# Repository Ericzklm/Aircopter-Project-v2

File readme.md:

# Aircopter Project

This project was done in association with the IEEE Student Branch on the UCLA campus.
This is the second iteration of the project. Due to the 2020 global pandemic, this
project was cut short for the 2019-2020 academic year and will resume in the 2020-
2021 academic year.

The goal of the project was to: 1. Design and assemble a custom PCB for a drone,
2. Write a program to hover the drone, then fly the drone. Because of the nature
of the project, the PCB was required to be small and compact (meaning SMD soldering
was needed) and the program needed to be quick and responsive.

#### Note: 

This version of the project was cut short due to the 2020 pandemic. The code was still
written and the board was still designed and printed but we were not able to assemble
and solder the final product because we were then living off-campus and all campus
activities we're mandated to be put on hold.

### Hardware Selection Choices:

**MCU**: The main chip is the model STM32F405. This was chosen for its ideal balance
between size and functionality. It is able to support all the needed sensors and
motor drivers for our drone and can be powered by a 3.3v supply which closely
matches the 3.7v of standard drone batteries (3.7v is stepped down to 3.3 using
a voltage regulator). Additionally, this chip was more ideal than other chips of
similar style because it handles floating point calculations better which allows
for simplicity and efficiency when writing the program.

**Voltage Regulator**: The voltage regulator used is the LTC3246MPMSE from Linear 
Technology. This component was chosen since it is a buck boost regulator with
the ability to step down or step up voltage as we need in this application. This
component is larger, more expensive, and more complex than the regulator used in
the first iteration but it accomplishes the same purpose while being much easier
to solder onto the board (no heat guns required).

**Wireless Module**: The wireless module used is the nrf24l01 which is standard, easy
to use, and familiar so we used it in this application since it fits well with the
acclerometer module.

**Accelerometer/Gyroscope**: The module used is the mpu6050 which is standard, easy to
use, and familiar so we used it in this application since it fits well with the
wireless module.

**Oscillator**: We opted for an abracon 25mhz crystal oscillator. The frequency fits 
the range of our operation and takes up a relatively small amount of space on
the PCB. In this iteration, a through-hole component was chosen because it could
be added more compactly without needing large pads on the PCB outside the area of
the oscillator.

**Passive Components**: For the resistors, capacitors, and inductors, we primarily
used parts with the package size 0603 which would fit the board without being
overly difficult to solder. Each piece was checked for its operating voltages as 
well as the operating temperatures to make sure no issues would arise. Additonally,
we tried to get components that were less dependent on external passive components
so we could make the PCB more compact/efficient.

### Hardware Design Choices:

**Motors**: In this design, we opted to place the 4 motor JST connectors along the left
side of the board because this would reduce the amount of "prime-real-estate" occupied
by the motor drivers. Also, we saved a significant amount of space on the PCB by
moving the motor drivers to the backside, under the JST rather than having the drivers
being on the same side (which means we cannot overlap the area occupied by the JSTs).

**Battery**: The JST of the battery is placed directly right of the motors. This is
important since its a central component and that position allows it easy access to
the motors and the rest of the PCB.

**Voltage Regulator**: The voltage regulator is placed below the battery JST, also in a
central position. This is key because we are able to define the 3.7V and 3.3V polygons
without complexity, and therefore reduing bottlenecks. Because the voltage regulator
is dependent on several passive components, it is placed in an open space with the
passive components compactly fit around it, without creating any major bottlenecks.

**Polygons**: Because of the location of the voltage divider, we are able to make an easy
distinction between the 3.3v, 3.7v, motor ground, and general ground planes. Everything
left of the voltage regulator is either the 3.7v or motor ground planes while everything
right is either 3.3v or general ground.

**MCU**: We chose to turn the MCU 45 degrees for a few reasons:
  1. Having the MCU turned actually signficantly reduced the bottlenecks as key 
  components had more direct access to the 3.3v plane and we had less "dead-ends" in 
  the plane. This gave extra space to work in that would not present a threat of 
  bottlenecking.
  2. The traces coming out of the MCU can be shorter and more optimized for the key
  components.
  3. We thought it looked neat!

**Oscillator**: The oscillator is placed as physically close to the MCU as possible with
relatively thick traces in order to prevent that signal from being overly distorted.

**Wireless Module/Accelerometer**: Because these two modules are not raised to the same
level, they can be overlapping on the PCB and not cause any issues. The wireless
module is placed along the right side while the accelerometer is placed along the
bottom because this allows for easy access to the respective connections on the MCU.

**Other items**: This includes the programmer and the reset switch. Since neither of them
are crucial in the operation of the drone, they are place along the top with less
direct connections (meaning the traces and planes for key components are better
optimized). Additionally, this iteration includes a tx and rx connection which will
be useful for debugging.

**Bottlenecks**: For this version, we were able to get away with no major bottlenecks
in the planes thanks to the reduction of passive components, better placements,
and the 45 degree MCU.

**Decoupling Capacitors**: The decoupling capacitors are placed in such a way that they
are close to the components they stabalize. This also helped in reducing bottlenecks
as passive components were not cutting up the planes

### Possible Improvements:

Some components are not optimally placed meaning the traces are not direct. This can
be solved by either tweaking the placement or choosing different compatible pins on
the MCU. Also the placement of the motors and battery mean that the lower motors are
further away from the power source, meaning potentially higher noise. Furthermore,
adding some LEDs would be useful for debugging (we have the room to do so).

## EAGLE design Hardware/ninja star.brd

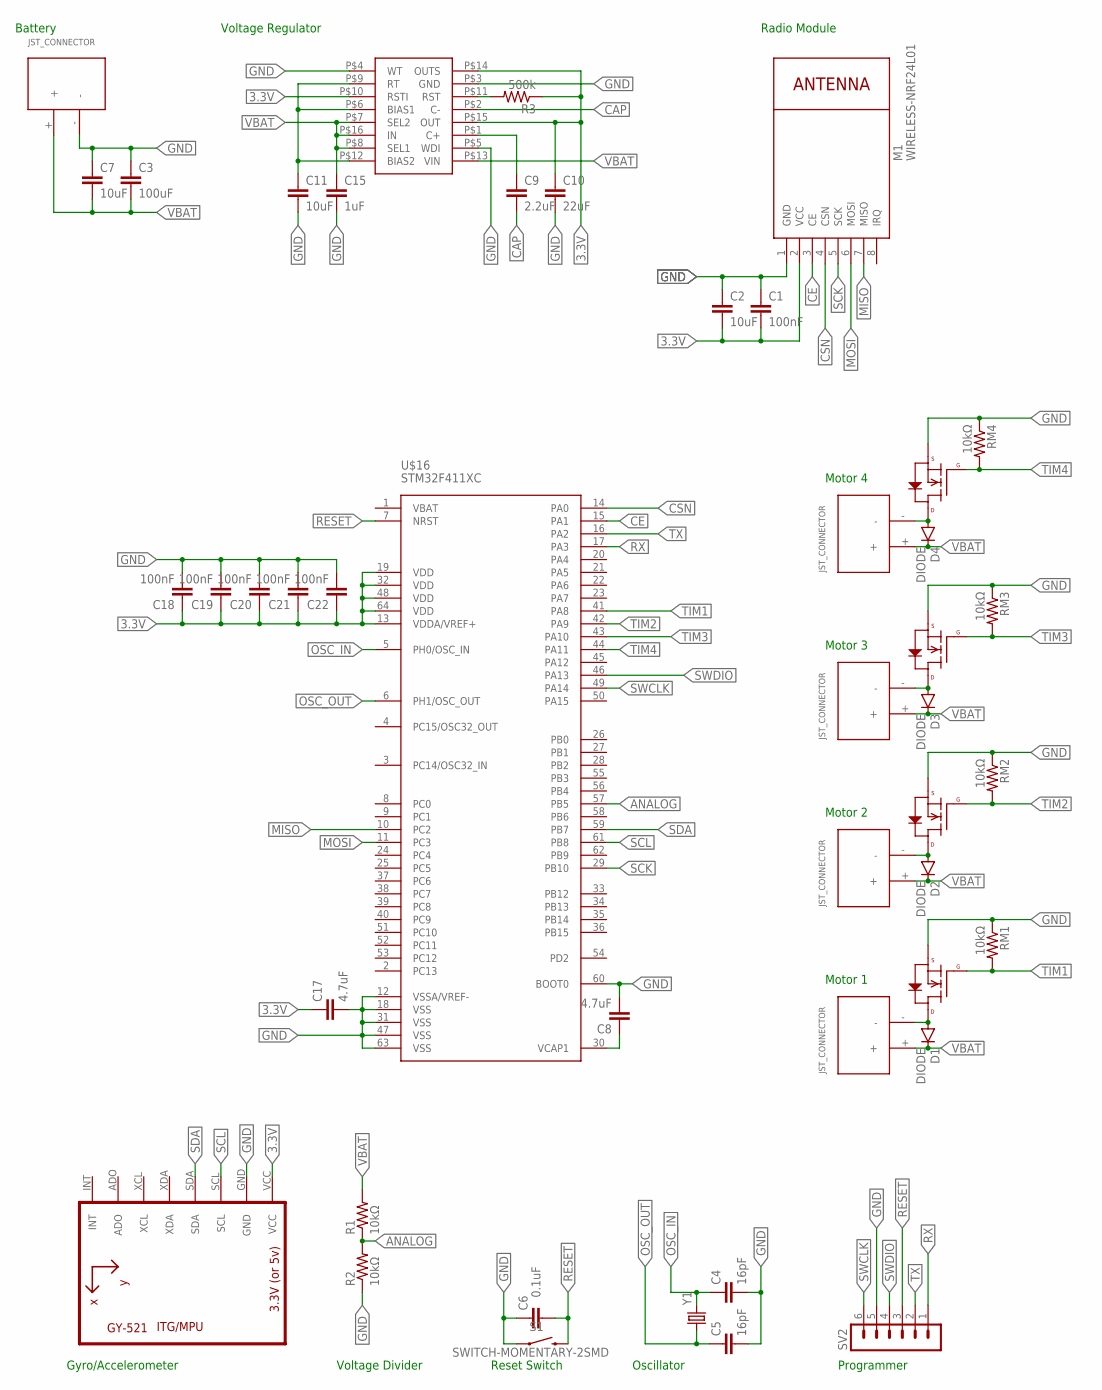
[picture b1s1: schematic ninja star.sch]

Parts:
C1, C18, C19, C20, C21, C22: 100nF; C0603
C2, C7, C11: 10uF; C0603
C3: 100uF; C1206
C4, C5: 16pF; C0603
C6: 0.1uF; C0603
C8, C17: 4.7uF; C0603
C9: 2.2uF; C0603
C10: 22uF; C0603
C15: 1uF; C0603
D1, D2, D3, D4: DIODE; C0603
M1: WIRELESS-NRF24L01
MOS1, MOS2, MOS3, MOS4: N-CHANNEL-MOSFET-IRLML6244TRPBF; SOT23-3
MOTOR1, MOTOR2, MOTOR3, MOTOR4: JST_CONNECTOR_FEMALE
R1, R2: 10kΩ; R0603
R3: 500k; R0603
RM1, RM2, RM3, RM4: 10kΩ; R0603
S1: SWITCH-MOMENTARY-2SMD; TACTILE-SWITCH-SMD
SV2: MA06-1
U1: GY-521MPU6050; GY-521
U$7: JST_CONNECTOR_FEMALE
U$12: VR-LTC3246; MSOP-16
U$16: STM32F411XC; LQFP64
Y1: CRYSTALHC49US; HC49US

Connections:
3.3V: C1.2, C2.2, C10.1, C17.1, C18.1, C19.1, C20.1, C21.1, C22.1, M1.2 (VCC), R3.1, U1.VCC, U$12.P$10 (RSTI), U$12.P$14 (OUTS), U$12.P$15 (OUT), U$16.13 (VDDA/VREF+), U$16.19 (VDD), U$16.32 (VDD), U$16.48 (VDD), U$16.64 (VDD)
ANALOG: R1.1, R2.2, U$16.57 (PB5)
CAP: C9.2, U$12.P$2 (C-)
CE: M1.3 (CE), U$16.15 (PA1)
CSN: M1.4 (CSN), U$16.14 (PA0)
GND: C1.1, C2.1, C3.1, C4.2, C5.2, C6.1, C7.1, C8.2, C10.2, C11.2, C15.2, C17.2, C18.2, C19.2, C20.2, C21.2, C22.2, M1.1 (GND), MOS1.2 (S), MOS2.2 (S), MOS3.2 (S), MOS4.2 (S), R2.1, RM1.1, RM2.1, RM3.1, RM4.1, S1.1, SV2.5, U1.GND, U$7.-, U$12.P$3 (GND), U$12.P$4 (WT), U$12.P$5 (WDI), U$16.12 (VSSA/VREF-), U$16.18 (VSS), U$16.31 (VSS), U$16.47 (VSS), U$16.60 (BOOT0), U$16.63 (VSS)
MISO: M1.7 (MISO), U$16.10 (PC2)
MOSI: M1.6 (MOSI), U$16.11 (PC3)
unnamed: C9.1, U$12.P$1 (C+)
unnamed: D2.2 (PPIN), MOS2.3 (D), MOTOR2.-
unnamed: D1.2 (PPIN), MOS1.3 (D), MOTOR1.-
unnamed: D3.2 (PPIN), MOS3.3 (D), MOTOR3.-
unnamed: D4.2 (PPIN), MOS4.3 (D), MOTOR4.-
unnamed: R3.2, U$12.P$11 (RST)
unnamed: C8.1, U$16.30 (VCAP1)
unnamed: C11.1, U$12.P$6 (BIAS1), U$12.P$9 (RT), U$12.P$12 (BIAS2)
OSC_IN: C4.1, U$16.5 (PH0/OSC_IN), Y1.2
OSC_OUT: C5.1, U$16.6 (PH1/OSC_OUT), Y1.1
RESET: C6.2, S1.3 (2), SV2.3, U$16.7 (NRST)
RX: SV2.1, U$16.17 (PA3)
SCK: M1.5 (SCK), U$16.29 (PB10)
SCL: U1.SCL, U$16.61 (PB8)
SDA: U1.SDA, U$16.59 (PB7)
SWCLK: SV2.6, U$16.49 (PA14)
SWDIO: SV2.4, U$16.46 (PA13)
TIM1: MOS1.1 (G), RM1.2, U$16.41 (PA8)
TIM2: MOS2.1 (G), RM2.2, U$16.42 (PA9)
TIM3: MOS3.1 (G), RM3.2, U$16.43 (PA10)
TIM4: MOS4.1 (G), RM4.2, U$16.44 (PA11)
TX: SV2.2, U$16.16 (PA2)
VBAT: C3.2, C7.2, C15.1, D1.1 (GPIN), D2.1 (GPIN), D3.1 (GPIN), D4.1 (GPIN), MOTOR1.+, MOTOR2.+, MOTOR3.+, MOTOR4.+, R1.2, U$7.+, U$12.P$7 (SEL2), U$12.P$8 (SEL1), U$12.P$13 (VIN), U$12.P$16 (IN)

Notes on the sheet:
Battery
Voltage Divider
Voltage Regulator
Radio Module
Motor 4
Motor 3
Motor 2
Motor 1
Gyro/Accelerometer
Reset Switch
Oscillator
Programmer

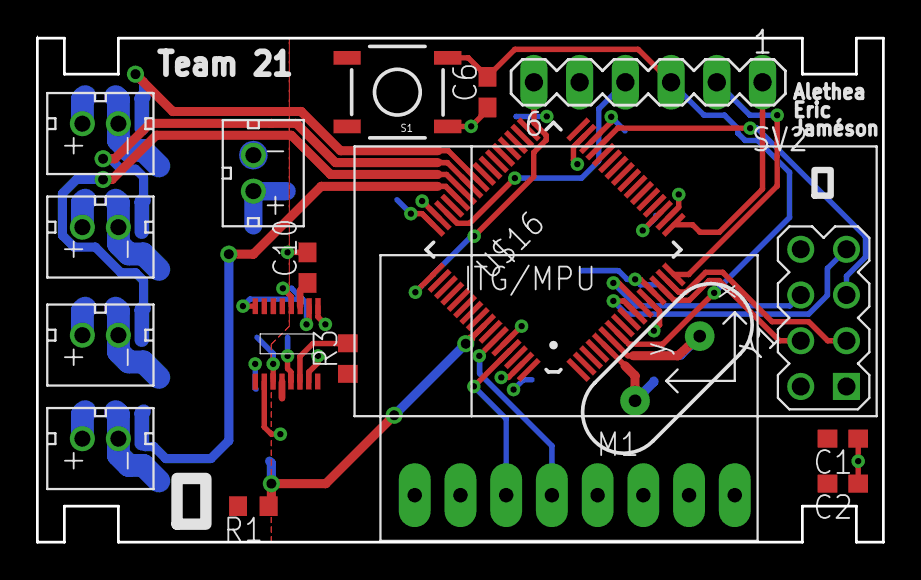
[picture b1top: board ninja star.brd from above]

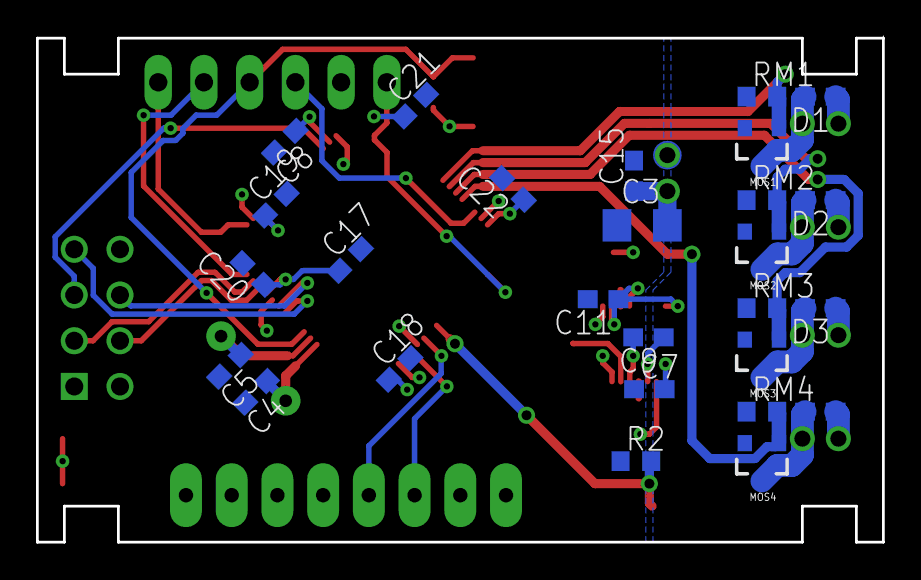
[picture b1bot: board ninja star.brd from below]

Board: 2 copper layers, 47.0 x 28.0 mm, 45 parts (27 on the bottom side), 31 nets.

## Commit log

2020-08-13 Added Hardware Changes and Files.
2020-08-15 Documentation Update.
2020-08-19 Bug Fixes, Organization, and Documentation.
